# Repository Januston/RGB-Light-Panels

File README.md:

# RGB-Light-Panels
🎨 Custom RGB panel designed for a prom sign, engineered to work with low voltage using Eagle 🦅. While the chip normally couldn't control eight 4-pin LEDs simultaneously, I leveraged NPN transistors and multiplexing. This technique rapidly switches LEDs on and off, making them seem illuminated simultaneously to the human eye—a blend of electronics and optical illusion.

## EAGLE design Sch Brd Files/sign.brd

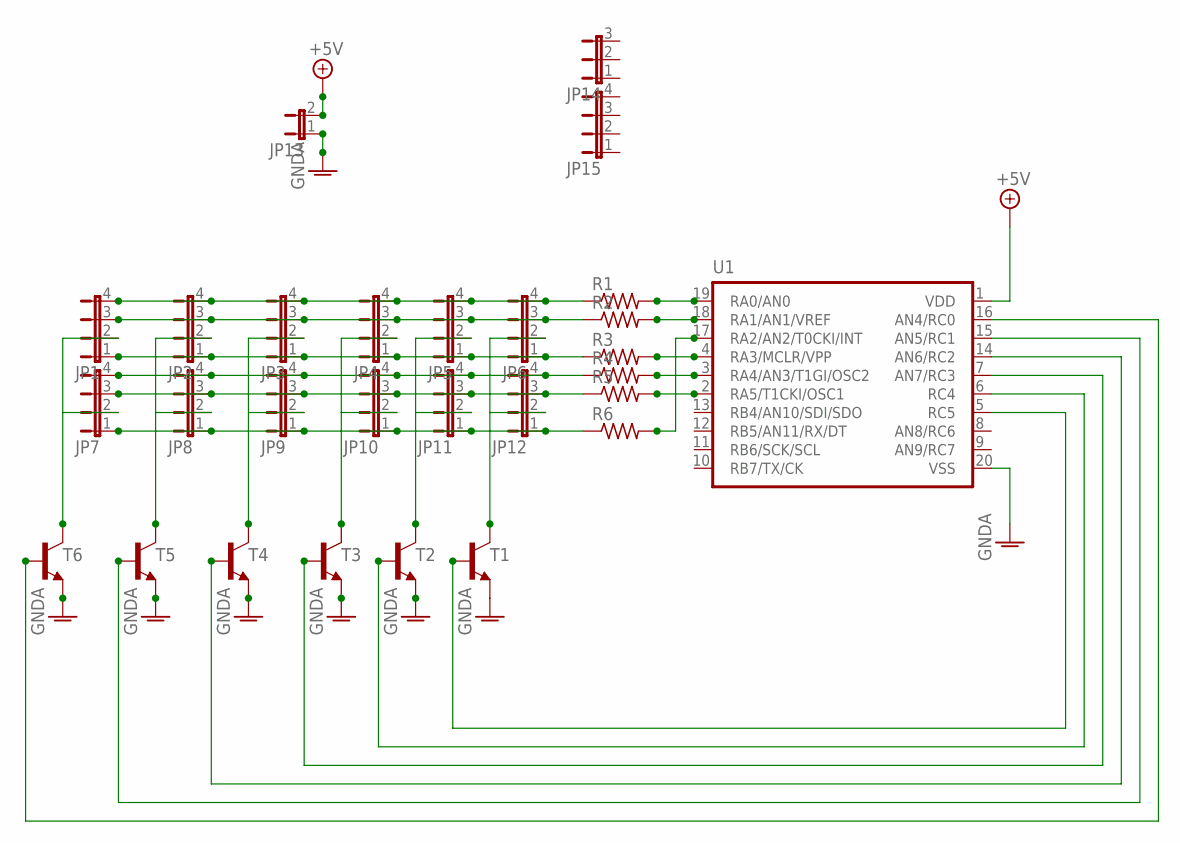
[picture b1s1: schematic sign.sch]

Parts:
JP1, JP2, JP3, JP4, JP5, JP6, JP7, JP8, JP9, JP10, JP11, JP12, JP15: JP4E; JP4
JP13: JP1E; JP1
JP14: JP2E; JP2
R1, R2, R3, R4, R5, R6: R-US_0207/10; 0207/10
T1, T2, T3, T4, T5, T6: -NPN-TO92; TO92
U1: PIC16F6XX; DIL20

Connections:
+5V: JP13.2, U1.1 (VDD)
GNDA: JP13.1, T1.1 (E), T2.1 (E), T3.1 (E), T4.1 (E), T5.1 (E), T6.1 (E), U1.20 (VSS)
unnamed: R1.2, U1.19 (RA0/AN0)
unnamed: R2.2, U1.18 (RA1/AN1/VREF)
unnamed: R3.2, U1.4 (RA3/MCLR/VPP)
unnamed: R4.2, U1.3 (RA4/AN3/T1GI/OSC2)
unnamed: R5.2, U1.2 (RA5/T1CKI/OSC1)
unnamed: R6.2, U1.17 (RA2/AN2/T0CKI/INT)
unnamed: JP1.4, JP2.4, JP3.4, JP4.4, JP5.4, JP6.4, R1.1
unnamed: JP1.2, JP7.2, T6.3 (C)
unnamed: JP2.2, JP8.2, T5.3 (C)
unnamed: JP3.2, JP9.2, T4.3 (C)
unnamed: JP4.2, JP10.2, T3.3 (C)
unnamed: JP5.2, JP11.2, T2.3 (C)
unnamed: JP1.3, JP2.3, JP3.3, JP4.3, JP5.3, JP6.3, R2.1
unnamed: JP1.1, JP2.1, JP3.1, JP4.1, JP5.1, JP6.1, R3.1
unnamed: JP7.4, JP8.4, JP9.4, JP10.4, JP11.4, JP12.4, R4.1
unnamed: JP7.3, JP8.3, JP9.3, JP10.3, JP11.3, JP12.3, R5.1
unnamed: JP6.2, JP12.2, T1.3 (C)
unnamed: JP7.1, JP8.1, JP9.1, JP10.1, JP11.1, JP12.1, R6.1
unnamed: T6.2 (B), U1.16 (AN4/RC0)
unnamed: T5.2 (B), U1.15 (AN5/RC1)
unnamed: T4.2 (B), U1.14 (AN6/RC2)
unnamed: T3.2 (B), U1.7 (AN7/RC3)
unnamed: T2.2 (B), U1.6 (RC4)
unnamed: T1.2 (B), U1.5 (RC5)

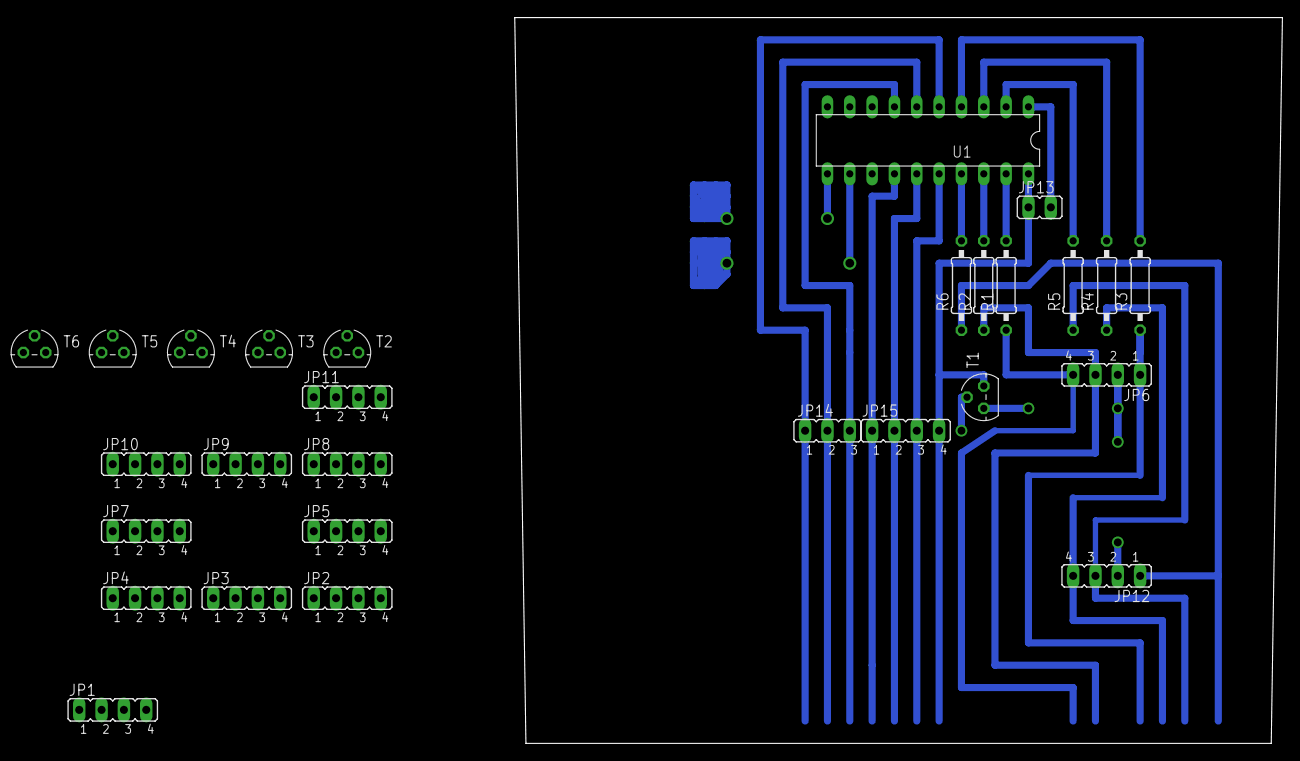
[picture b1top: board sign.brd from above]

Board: 2 copper layers, 87.3 x 82.5 mm, 28 parts (0 on the bottom side), 26 nets.

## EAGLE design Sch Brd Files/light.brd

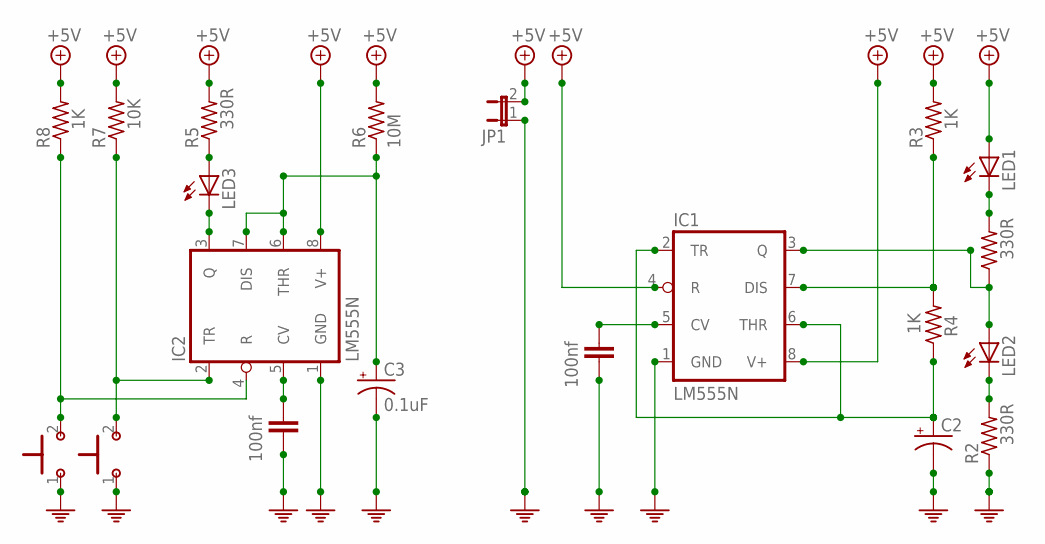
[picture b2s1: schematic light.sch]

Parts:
C1, C4: 100nf; C050-025X075
C2: CPOL-USE5-9VAXIAL; E5R
C3: 0.1uF; E5R
IC1, IC2: LM555N; DIL08
JP1: JP1E; JP1
LED1, LED2, LED3: LED5MM
R1, R2, R5: 330R; 0207/10
R3, R4, R8: 1K; 0207/10
R6: 10M; 0207/10
R7: 10K; 0207/10
U$1, U$2: PUSHBUTTON

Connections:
+5V: IC1.4 (R), IC1.8 (V+), IC2.8 (V+), JP1.2, LED1.A, R3.2, R5.2, R6.2, R7.2, R8.2
unnamed: IC1.3 (Q), LED2.A, R1.1
unnamed: C1.1, IC1.5 (CV)
unnamed: C2.+, IC1.2 (TR), IC1.6 (THR), R4.1
unnamed: LED2.K (C), R2.2
unnamed: IC1.7 (DIS), R3.1, R4.2
unnamed: LED1.K (C), R1.2
unnamed: C4.1, IC2.5 (CV)
unnamed: IC2.3 (Q), LED3.K (C)
unnamed: LED3.A, R5.1
unnamed: C3.+, IC2.6 (THR), IC2.7 (DIS), R6.1
unnamed: IC2.2 (TR), R7.1, U$1.2
unnamed: IC2.4 (R), R8.1, U$2.2
PE: C1.2, C2.-, C3.-, C4.2, IC1.1 (GND), IC2.1 (GND), JP1.1, R2.1, U$1.1, U$2.1

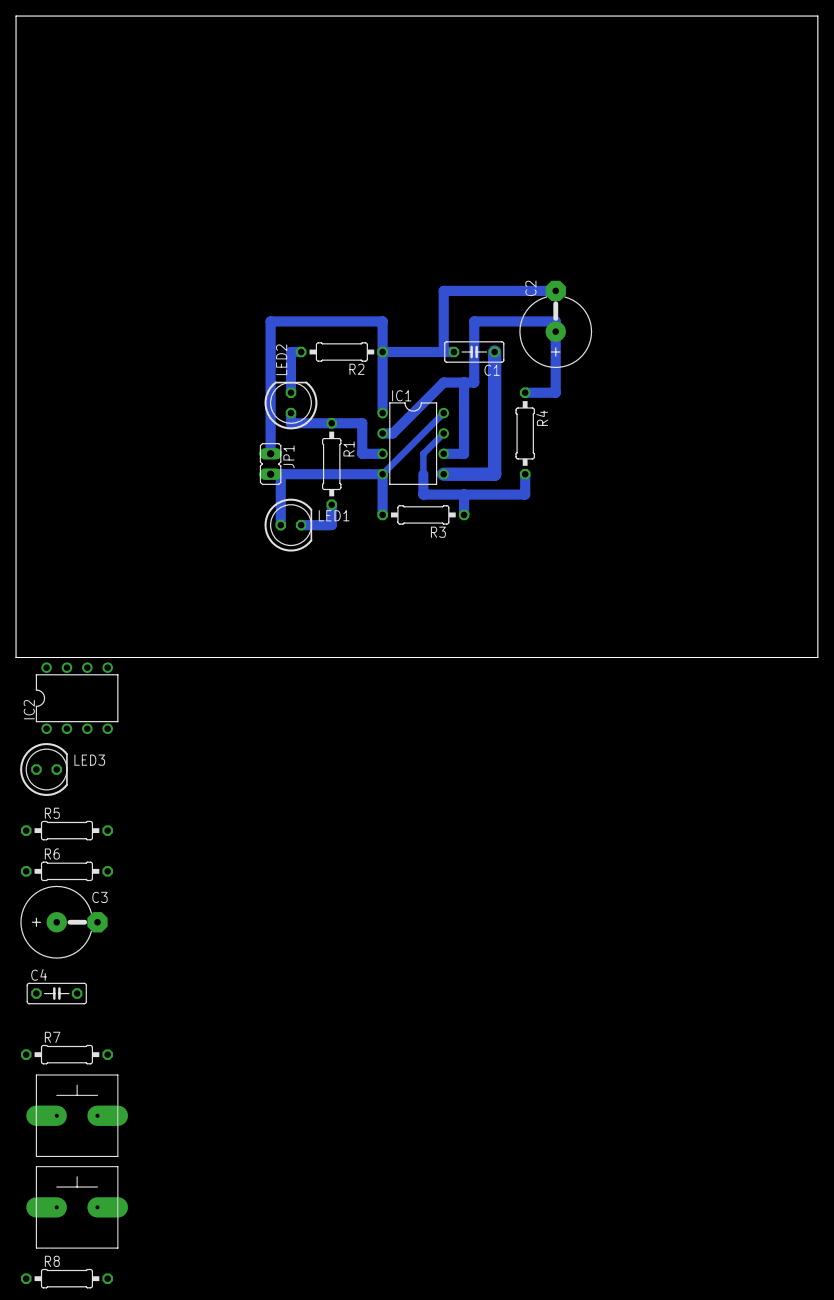
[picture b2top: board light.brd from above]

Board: 2 copper layers, 100.0 x 80.0 mm, 20 parts (0 on the bottom side), 14 nets.

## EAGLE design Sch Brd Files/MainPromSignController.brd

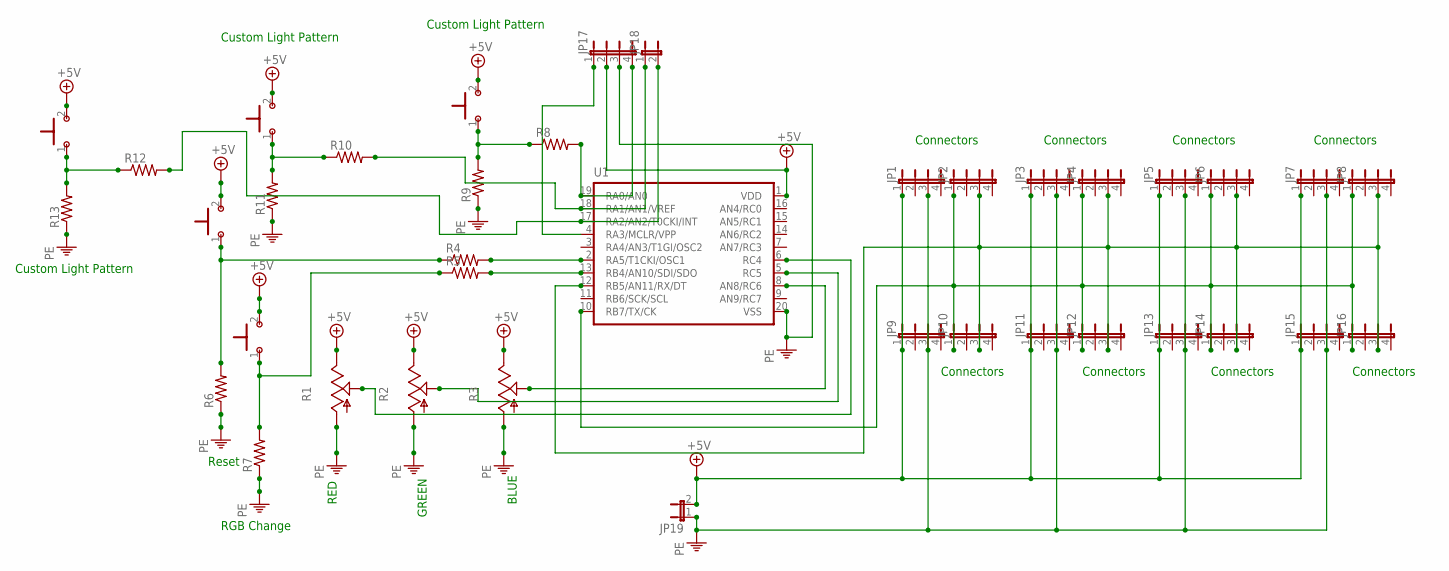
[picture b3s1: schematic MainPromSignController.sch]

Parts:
JP1, JP2, JP3, JP4, JP5, JP6, JP7, JP8, JP9, JP10, JP11, JP12, JP13, JP14, JP15, JP16, JP17: JP4E; JP4
JP18, JP19: JP1E; JP1
R1, R2, R3: TRIM_US-B25P; B25P
R4, R5, R6, R7, R8, R9, R10, R11, R12, R13: R-US_0207/10; 0207/10
U1: PIC16F6XX; DIL20
U$1, U$2, U$3, U$4, U$5: PUSHBUTTON

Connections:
+5V: JP1.1, JP3.1, JP5.1, JP7.1, JP9.1, JP11.1, JP13.1, JP15.1, JP17.2, JP19.2, R1.E, R2.E, R3.E, U1.1 (VDD), U$1.2, U$2.2, U$3.2, U$4.2, U$5.2
unnamed: R1.S, U1.6 (RC4)
unnamed: R2.S, U1.5 (RC5)
unnamed: R3.S, U1.8 (AN8/RC6)
unnamed: R4.2, U1.2 (RA5/T1CKI/OSC1)
unnamed: R5.2, U1.13 (RB4/AN10/SDI/SDO)
unnamed: R5.1, R7.2, U$2.1
unnamed: R4.1, R6.2, U$1.1
unnamed: JP17.1, U1.4 (RA3/MCLR/VPP)
unnamed: R8.1, R9.2, U$3.1
unnamed: JP2.3, JP4.3, JP6.3, JP8.3, JP10.3, JP12.3, JP14.3, JP16.3, U1.12 (RB5/AN11/RX/DT)
unnamed: R10.1, R11.2, U$4.1
unnamed: R12.1, R13.2, U$5.1
unnamed: JP18.2, R12.2, U1.17 (RA2/AN2/T0CKI/INT)
unnamed: JP17.4, R8.2, U1.19 (RA0/AN0)
unnamed: JP18.1, R10.2, U1.18 (RA1/AN1/VREF)
unnamed: JP2.1, JP4.1, JP6.1, JP8.1, JP10.1, JP12.1, JP14.1, JP16.1, U1.10 (RB7/TX/CK)
PE: JP1.3, JP3.3, JP5.3, JP7.3, JP9.3, JP11.3, JP13.3, JP15.3, JP17.3, JP19.1, R1.A, R2.A, R3.A, R6.1, R7.1, R9.1, R11.1, R13.1, U1.20 (VSS)

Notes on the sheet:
RED
BLUE
GREEN
RGB Change
Reset
Custom Light Pattern
Connectors

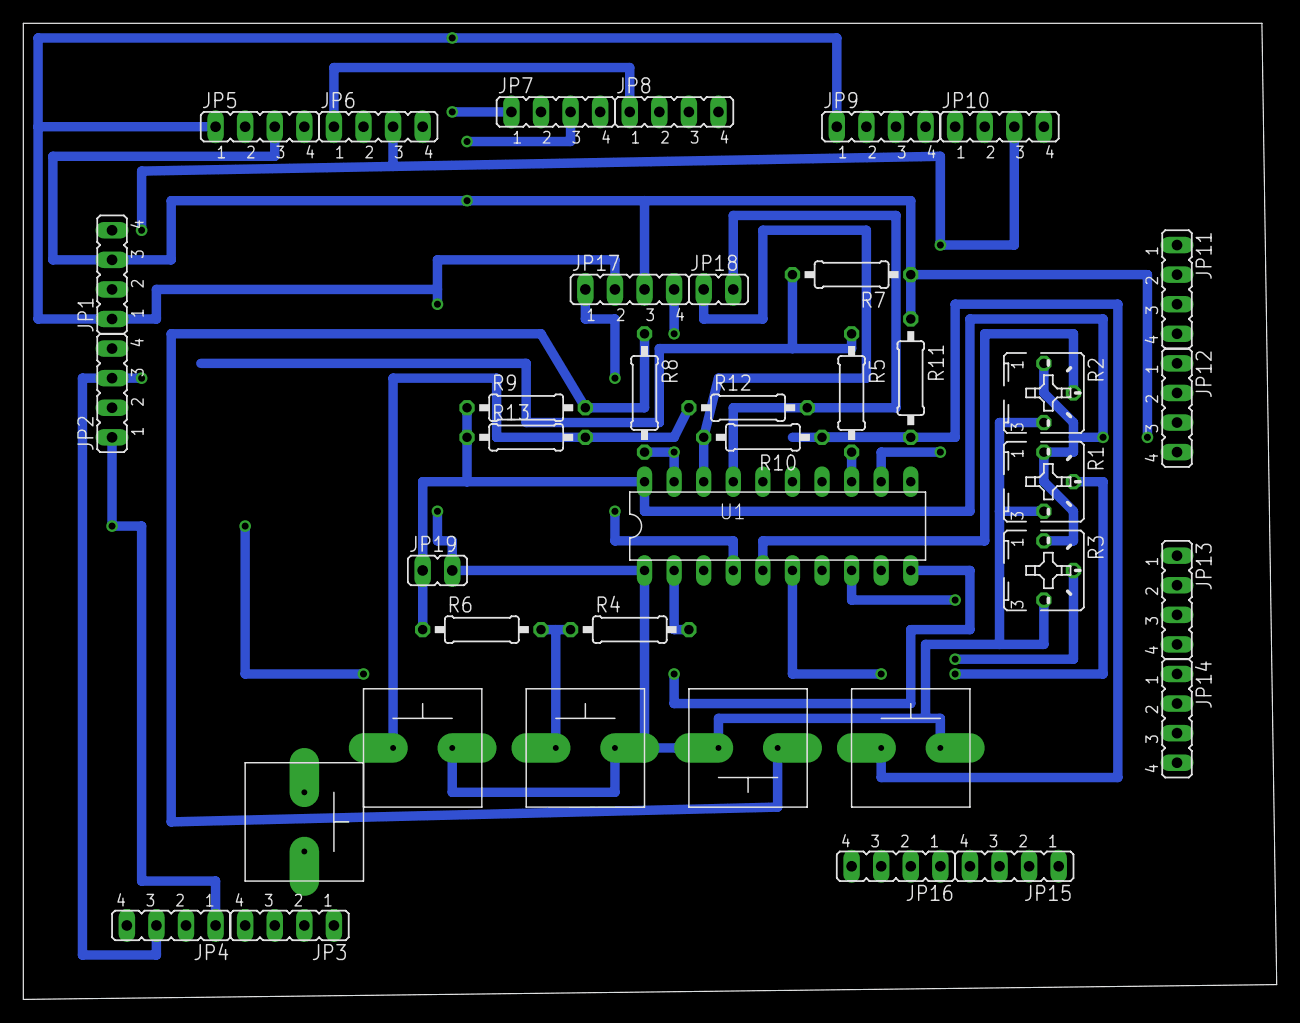
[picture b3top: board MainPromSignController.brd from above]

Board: 2 copper layers, 107.6 x 83.8 mm, 38 parts (0 on the bottom side), 18 nets.

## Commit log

2023-09-23 add Schematics and Traces
2023-09-23 upload schematics
2023-09-23 remove files
